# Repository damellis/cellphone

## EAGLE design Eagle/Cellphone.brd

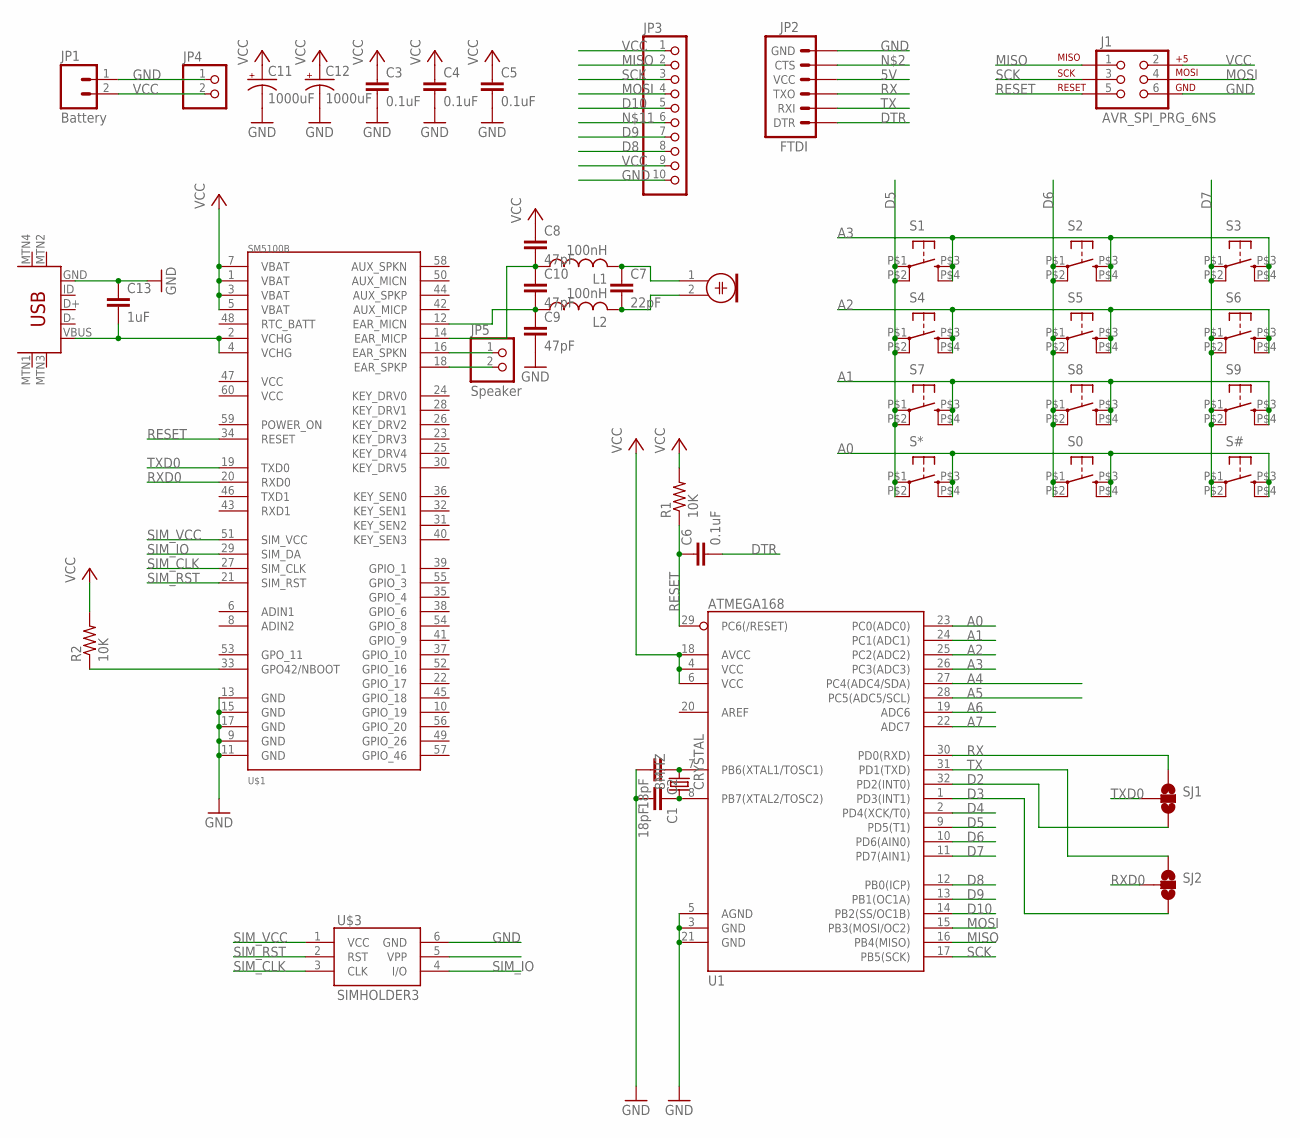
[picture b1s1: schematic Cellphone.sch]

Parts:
8MHZ: CRYSTAL; 2-SMD-5X3MM
C1, C2: 18pF; C1206
C3, C4, C5, C6: 0.1uF; C1206
C7: 22pF; C1206
C8, C9, C10: 47pF; C1206
C11, C12: 1000uF; D/7343-31R
C13: 1uF; C1206
J1: AVR_SPI_PRG_6NS; 2X3-NS
JP1: Battery; JST-2-SMD
JP2: FTDI; 1X06
JP3: TFT160X128; TFT1.8
JP4: PINHD-1X2; 1X02
JP5: Speaker; 1X02
L1, L2: 100nH; L2012C
M1: ELECTRET_MICROPHON-WM-64PC/64PK; WM-64PC/64PK
R1, R2: 10K; R1206
S0, S1, S2, S3, S4, S5, S6, S7, S8, S9: SWITCH-JLEAD; BUTTON_6MM_JLEAD
S#: SWITCH-JLEAD; BUTTON_6MM_JLEAD
S*: SWITCH-JLEAD; BUTTON_6MM_JLEAD
SJ1, SJ2: SOLDERJUMPER_2WAYPASTE1&2; SJ_3_PASTE1&2
U1: ATMEGA168; TQFP32-08
U$1: SM5100B
U$2: USB-MINIB-5PIN; USB-MINIB
U$3: SIMHOLDER3

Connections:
5V: JP2.4 (VCC)
A0: S0.P$3 (S), S0.P$4 (S1), S#.P$3 (S), S#.P$4 (S1), S*.P$3 (S), S*.P$4 (S1), U1.23 (PC0(ADC0))
A1: S7.P$3 (S), S7.P$4 (S1), S8.P$3 (S), S8.P$4 (S1), S9.P$3 (S), S9.P$4 (S1), U1.24 (PC1(ADC1))
A2: S4.P$3 (S), S4.P$4 (S1), S5.P$3 (S), S5.P$4 (S1), S6.P$3 (S), S6.P$4 (S1), U1.25 (PC2(ADC2))
A3: S1.P$3 (S), S1.P$4 (S1), S2.P$3 (S), S2.P$4 (S1), S3.P$3 (S), S3.P$4 (S1), U1.26 (PC3(ADC3))
A4: U1.27 (PC4(ADC4/SDA))
A5: U1.28 (PC5(ADC5/SCL))
A6: U1.19 (ADC6)
A7: U1.22 (ADC7)
D2: SJ1.3, U1.32 (PD2(INT0))
D3: SJ2.3, U1.1 (PD3(INT1))
D4: U1.2 (PD4(XCK/T0))
D5: S1.P$1, S1.P$2 (P1), S4.P$1, S4.P$2 (P1), S7.P$1, S7.P$2 (P1), S*.P$1, S*.P$2 (P1), U1.9 (PD5(T1))
D6: S0.P$1, S0.P$2 (P1), S2.P$1, S2.P$2 (P1), S5.P$1, S5.P$2 (P1), S8.P$1, S8.P$2 (P1), U1.10 (PD6(AIN0))
D7: S3.P$1, S3.P$2 (P1), S6.P$1, S6.P$2 (P1), S9.P$1, S9.P$2 (P1), S#.P$1, S#.P$2 (P1), U1.11 (PD7(AIN1))
D8: JP3.8 (RESET), U1.12 (PB0(ICP))
D9: JP3.7 (D/C), U1.13 (PB1(OC1A))
D10: JP3.5 (TFT_CS), U1.14 (PB2(SS/OC1B))
DTR: C6.2, JP2.1 (DTR)
GND: C1.2, C2.2, C3.2, C4.2, C5.2, C9.2, C11.-, C12.-, C13.1, J1.6, JP1.1 (2), JP2.6 (GND), JP3.10 (GND), JP4.1, U1.3 (GND), U1.5 (AGND), U1.21 (GND), U$1.9 (GND), U$1.11 (GND), U$1.13 (GND), U$1.15 (GND), U$1.17 (GND), U$2.GND, U$3.6 (GND)
MISO: J1.1, JP3.2 (MISO), U1.16 (PB4(MISO))
MOSI: J1.4, JP3.4 (MOSI), U1.15 (PB3(MOSI/OC2))
unnamed: R2.1, U$1.33 (GPO42/NBOOT)
unnamed: 8MHZ.P$2 (2), C2.1, U1.7 (PB6(XTAL1/TOSC1))
unnamed: 8MHZ.P$1 (1), C1.1, U1.8 (PB7(XTAL2/TOSC2))
unnamed: C7.1, L1.2, M1.1
unnamed: C7.2, L2.2, M1.2
unnamed: C8.2, C10.1, L1.1, U$1.14 (EAR_MICP)
unnamed: C9.1, C10.2, L2.1, U$1.12 (EAR_MICN)
unnamed: C13.2, U$1.2 (VCHG), U$1.4 (VCHG), U$2.VBUS
unnamed: JP5.1, U$1.16 (EAR_SPKN)
unnamed: JP5.2, U$1.18 (EAR_SPKP)
RESET: C6.1, J1.5, R1.1, U1.29 (PC6(/RESET)), U$1.34 (RESET)
RX: JP2.3 (TXO), SJ1.1, U1.30 (PD0(RXD))
RXD0: SJ2.2, U$1.20 (RXD0)
SCK: J1.3, JP3.3 (SCK), U1.17 (PB5(SCK))
SIM_CLK: U$1.27 (SIM_CLK), U$3.3 (CLK)
SIM_IO: U$1.29 (SIM_DA), U$3.4 (I/O)
SIM_RST: U$1.21 (SIM_RST), U$3.2 (RST)
SIM_VCC: U$1.51 (SIM_VCC), U$3.1 (VCC)
TX: JP2.2 (RXI), SJ2.1, U1.31 (PD1(TXD))
TXD0: SJ1.2, U$1.19 (TXD0)
VCC: C3.1, C4.1, C5.1, C8.1, C11.+, C12.+, J1.2, JP1.2 (1), JP3.1 (LITE), JP3.9 (VCC), JP4.2, R1.2, R2.2, U1.4 (VCC), U1.6 (VCC), U1.18 (AVCC), U$1.1 (VBAT), U$1.3 (VBAT), U$1.5 (VBAT), U$1.7 (VBAT)

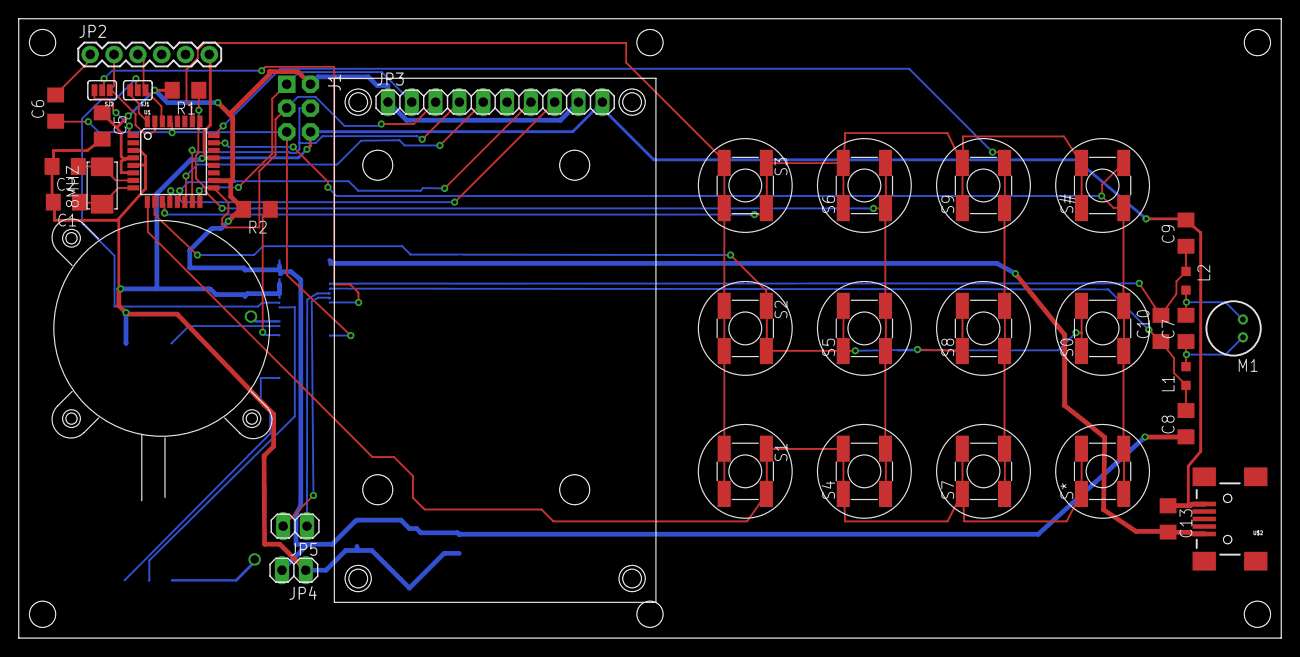
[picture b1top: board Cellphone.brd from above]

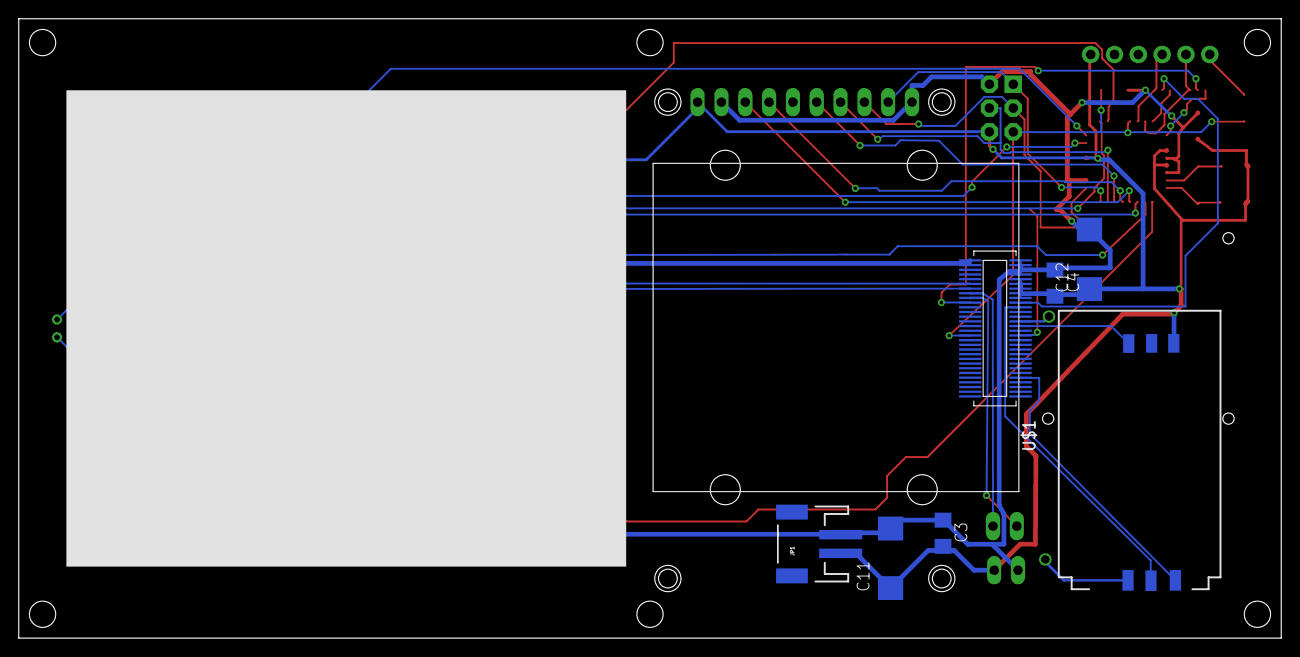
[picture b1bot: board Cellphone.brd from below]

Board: 2 copper layers, 134.6 x 66.0 mm, 44 parts (7 on the bottom side), 37 nets.

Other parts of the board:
U$5: SPEAKER_23MM

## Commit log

2012-03-19 Initial sketches.
2012-04-23 Adding libraries and keypad version of dialer.
2012-04-27 Moving Arduino code into "Arduino" folder.
2012-04-27 Adding Eagle files (circuit board) and Inkscape files (case).

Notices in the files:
parts and their libraries:
SparkFun-DigitalIC: Licensing: CC v3.0 Share-Alike You are welcome to use this library for commercial purposes.
